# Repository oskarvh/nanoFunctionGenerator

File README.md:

# nanoFunctionGenerator
Arbitrary function generator using the RP2040

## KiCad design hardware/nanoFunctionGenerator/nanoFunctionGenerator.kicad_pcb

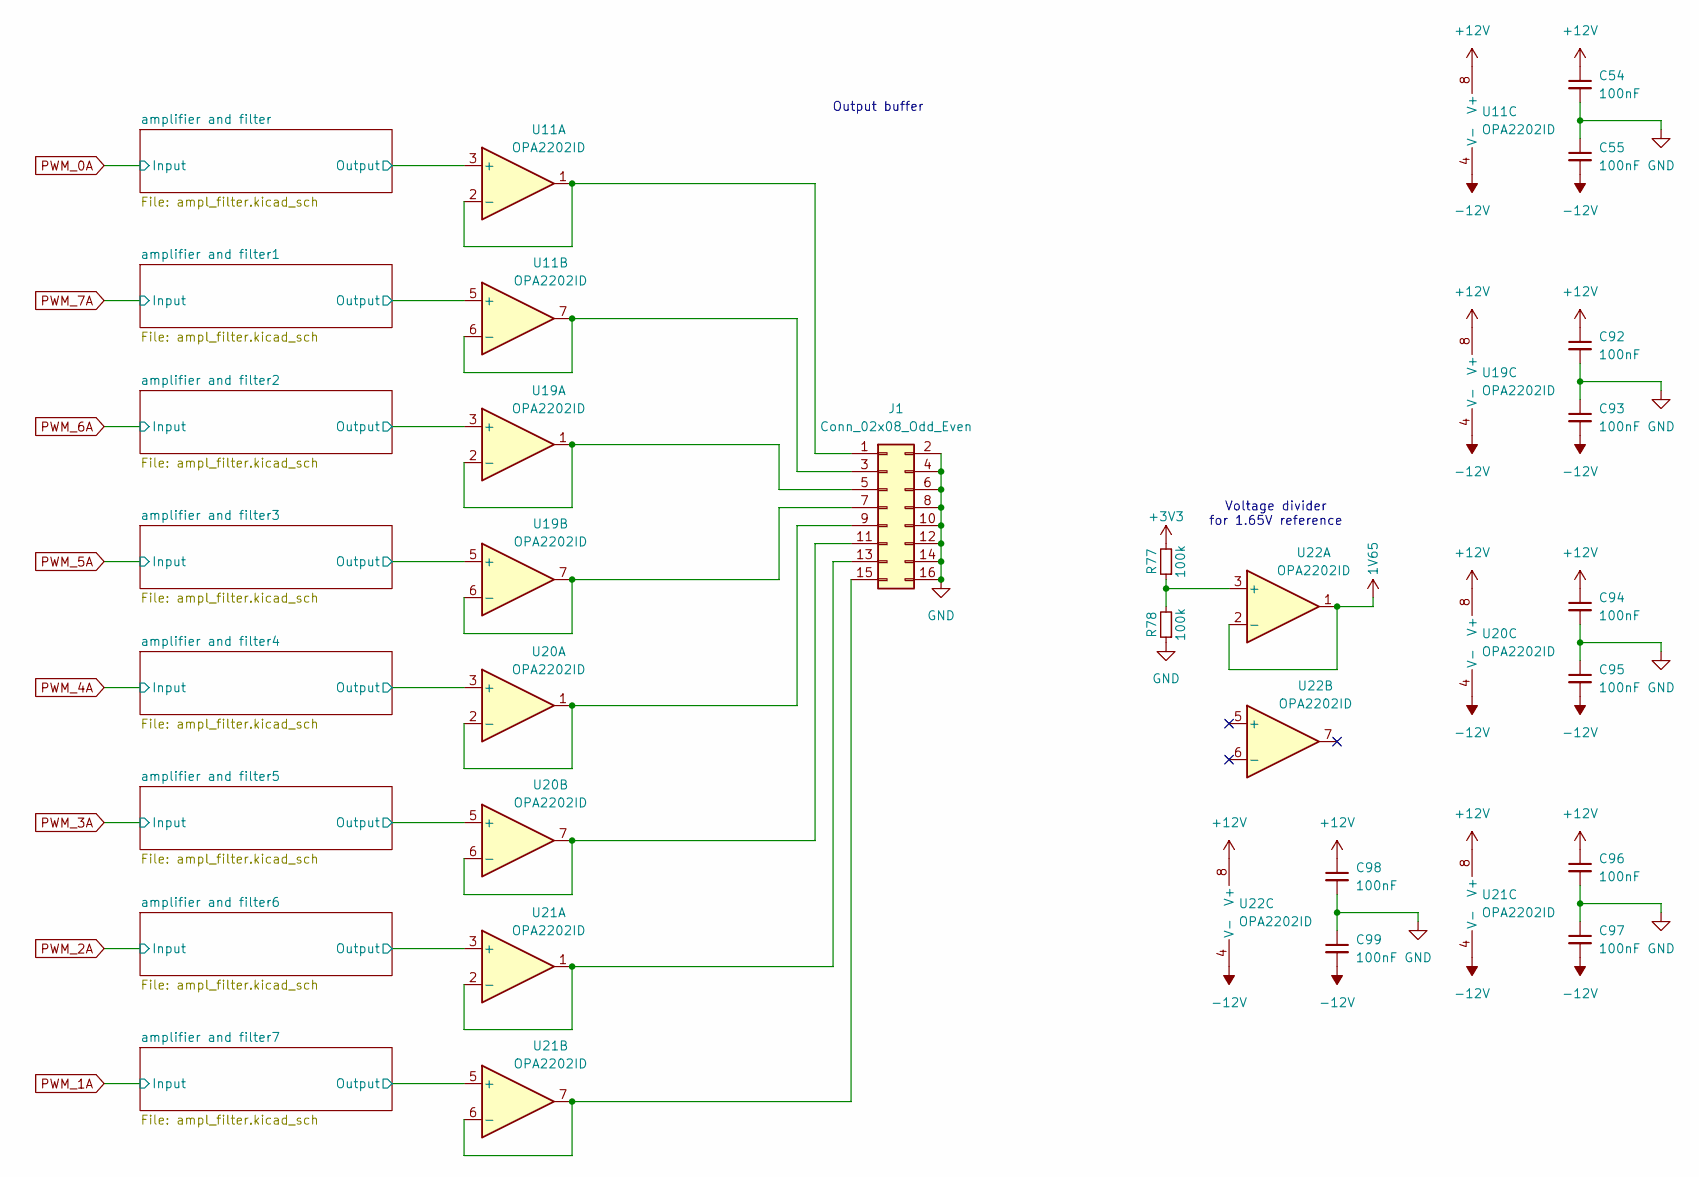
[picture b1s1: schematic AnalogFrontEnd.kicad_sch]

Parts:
C54, C55, C92, C93, C94, C95, C96, C97, C98, C99: 100nF; C_0402_1005Metric
J1: Conn_02x08_Odd_Even; PinHeader_2x08_P2.54mm_Vertical
R77, R78: 100k; R_0402_1005Metric
U11, U19, U20, U21, U22: OPA2202ID; SOIC-8_3.9x4.9mm_P1.27mm

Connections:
1V65: U22.1, U22.2 (-); also elsewhere on the board
+3V3: R77.2; also elsewhere on the board
+12V: C54.1, C92.1, C94.1, C96.1, C98.1, U11.8 (V+), U19.8 (V+), U20.8 (V+), U21.8 (V+), U22.8 (V+); also elsewhere on the board
-12V: C55.2, C93.2, C95.2, C97.2, C99.2, U11.4 (V-), U19.4 (V-), U20.4 (V-), U21.4 (V-), U22.4 (V-); also elsewhere on the board
/AnalogFrontEnd/amplifier and filter1/Output: U11.5 (+); also elsewhere on the board
/AnalogFrontEnd/amplifier and filter2/Output: U19.3 (+); also elsewhere on the board
/AnalogFrontEnd/amplifier and filter3/Output: U19.5 (+); also elsewhere on the board
/AnalogFrontEnd/amplifier and filter4/Output: U20.3 (+); also elsewhere on the board
/AnalogFrontEnd/amplifier and filter5/Output: U20.5 (+); also elsewhere on the board
/AnalogFrontEnd/amplifier and filter6/Output: U21.3 (+); also elsewhere on the board
/AnalogFrontEnd/amplifier and filter7/Output: U21.5 (+); also elsewhere on the board
/AnalogFrontEnd/amplifier and filter/Output: U11.3 (+); also elsewhere on the board
GND: C54.2, C55.1, C92.2, C93.1, C94.2, C95.1, C96.2, C97.1, C98.2, C99.1, J1.2, J1.4, J1.6, J1.8, J1.10, J1.12, J1.14, J1.16, R78.1; also elsewhere on the board
unnamed: J1.1, U11.1, U11.2 (-)
unnamed: J1.3, U11.6 (-), U11.7
unnamed: J1.5, U19.1, U19.2 (-)
unnamed: J1.7, U19.6 (-), U19.7
unnamed: J1.9, U20.1, U20.2 (-)
unnamed: J1.11, U20.6 (-), U20.7
unnamed: J1.13, U21.1, U21.2 (-)
unnamed: J1.15, U21.6 (-), U21.7
unnamed: R77.1, R78.2, U22.3 (+)

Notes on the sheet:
Voltage divider for 1.65V reference
Output buffer

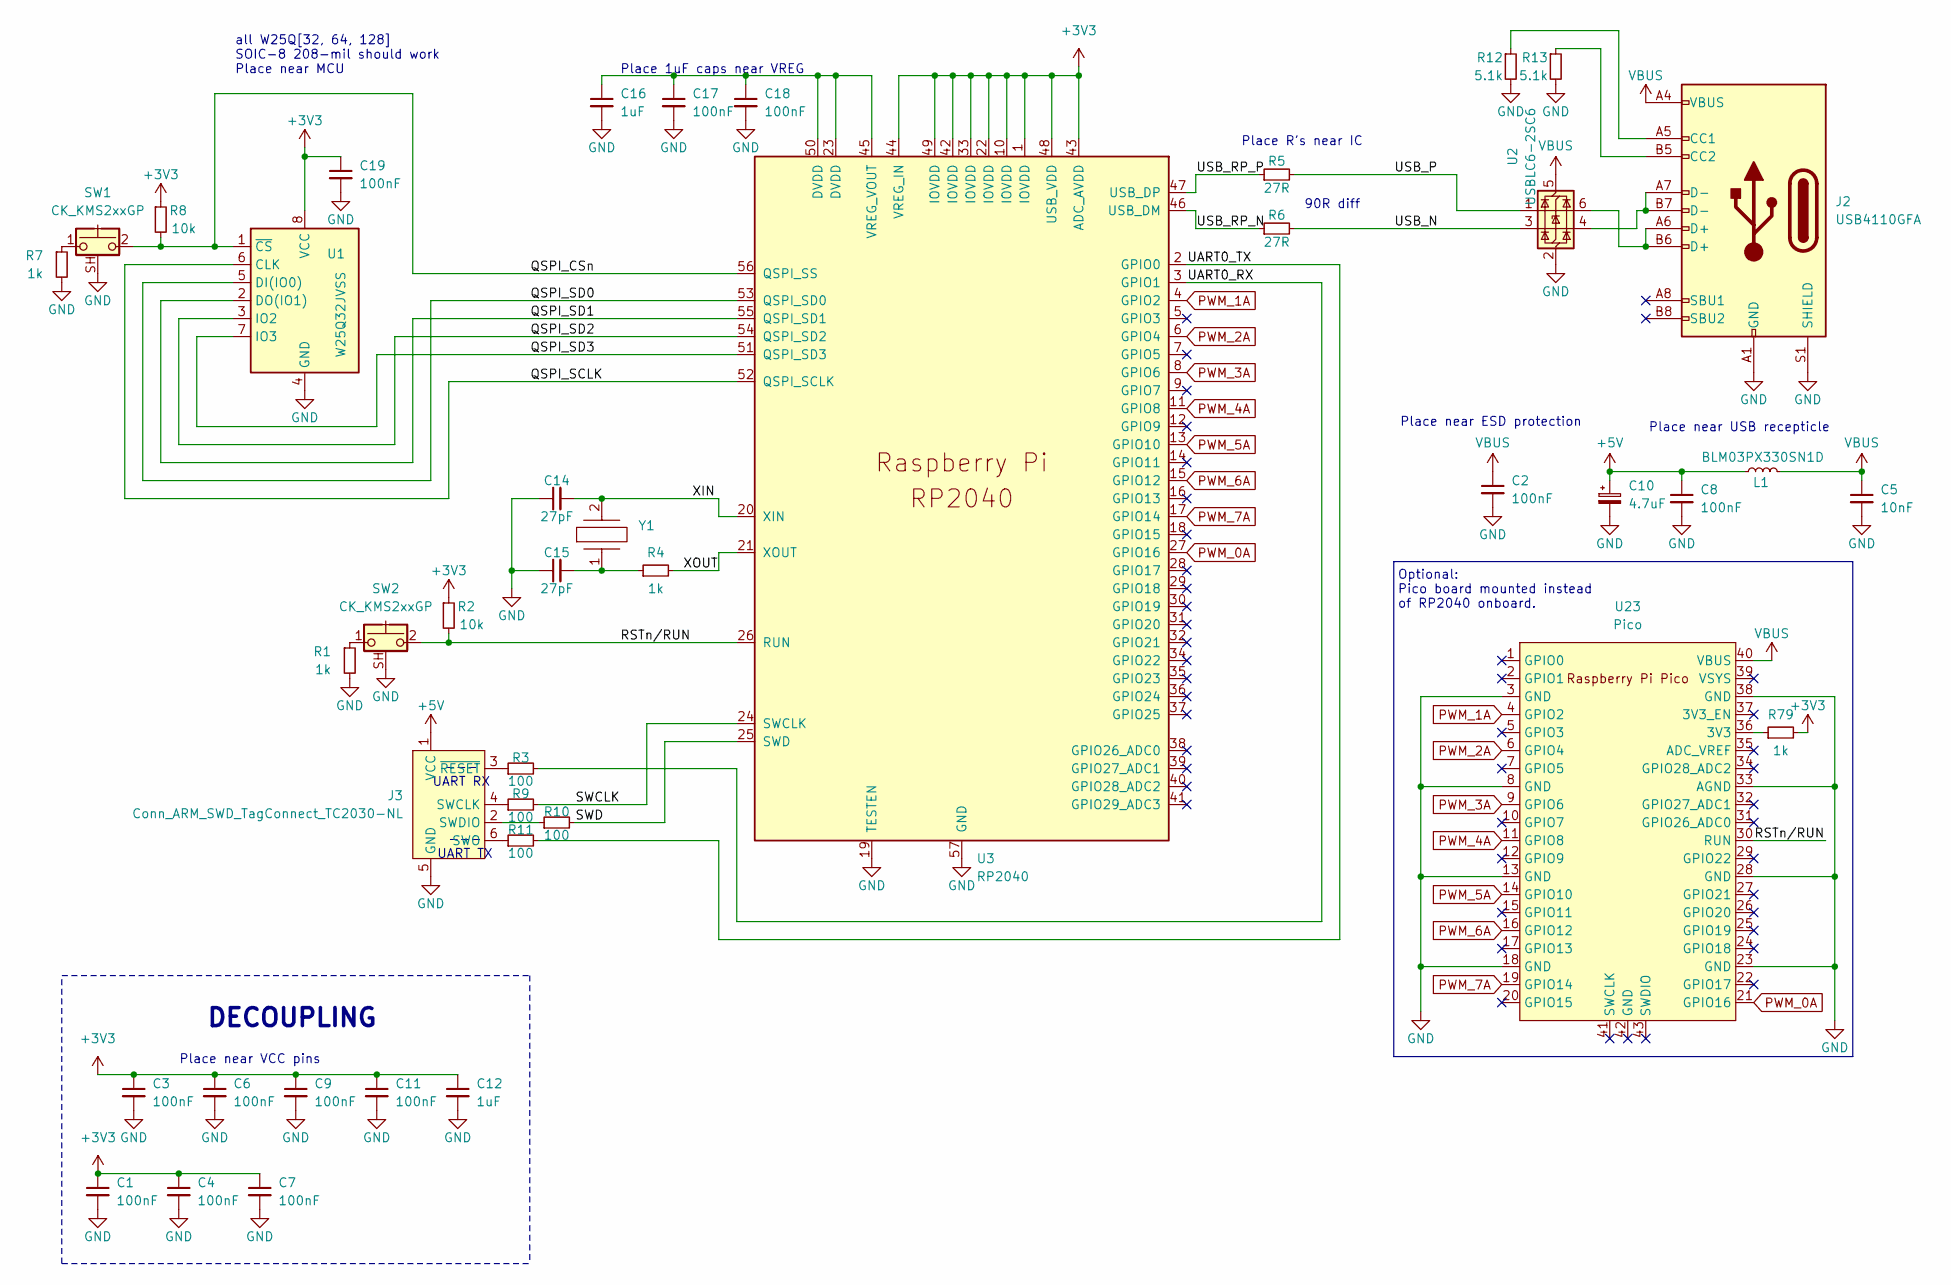
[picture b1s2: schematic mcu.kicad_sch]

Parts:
C1, C2, C3, C4, C6, C7, C8, C9, C11, C17, C18, C19: 100nF; C_0402_1005Metric; LCSC C1525
C5: 10nF; C_0402_1005Metric; LCSC C1525
C10: 4.7uF; C_Elec_4x5.4; Part Number 865080640004
C12, C16: 1uF; C_0402_1005Metric; LCSC C52923
C14, C15: 27pF; C_0402_1005Metric; LCSC C126504
J2: USB4110GFA; USB4110-GF-A_GCT
J3: Conn_ARM_SWD_TagConnect_TC2030-NL; Tag-Connect_TC2030-IDC-NL_2x03_P1.27mm_Vertical
L1: BLM03PX330SN1D; L_0603_1608Metric
R1, R7: 1k; R_0402_1005Metric; LCSC C279981
R2, R8: 10k; R_0402_1005Metric; LCSC C140214
R3, R9, R10, R11: 100; R_0402_1005Metric; LCSC C279981
R4, R79: 1k; R_0402_1005Metric; LCSC C11702
R5, R6: 27R; R_0402_1005Metric; LCSC C25100
R12, R13: 5.1k; R_0402_1005Metric; LCSC C279981
SW1, SW2: CK_KMS2xxGP; SW_SPST_CK_KMS2xxGP
U1: W25Q32JVSS; SOIC-8_5.23x5.23mm_P1.27mm
U2: USBLC6-2SC6; SOT-23-6
U3: RP2040; QFN-56-1EP_7x7mm_P0.4mm_EP3.2x3.2mm_ThermalVias; LCSC C2040
U23: Pico; RPi_Pico_SMD_TH
Y1: 445I23D12M00000; 445I23D12M00000_CTS-L; Mouser Part Number 774-445I23D12M00000

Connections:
+3V3: C1.1, C3.1, C4.1, C6.1, C7.1, C9.1, C11.1, C12.1, C19.1, R2.1, R8.1, R79.2, U1.8 (VCC), U3.1 (IOVDD), U3.10 (IOVDD), U3.22 (IOVDD), U3.33 (IOVDD), U3.42 (IOVDD), U3.43 (ADC_AVDD), U3.44 (VREG_IN), U3.48 (USB_VDD), U3.49 (IOVDD); also elsewhere on the board
+5V: C8.1, C10.1, J3.1 (VCC), L1.1; also elsewhere on the board
/mcu/QSPI_CSn: R8.2, SW1.2, U1.1 (~CS), U3.56 (QSPI_SS)
/mcu/QSPI_SCLK: U1.6 (CLK), U3.52 (QSPI_SCLK)
/mcu/QSPI_SD0: U1.5 (DI(IO0)), U3.53 (QSPI_SD0)
/mcu/QSPI_SD1: U1.2 (DO(IO1)), U3.55 (QSPI_SD1)
/mcu/QSPI_SD2: U1.3 (IO2), U3.54 (QSPI_SD2)
/mcu/QSPI_SD3: U1.7 (IO3), U3.51 (QSPI_SD3)
/mcu/RSTn/RUN: R2.2, SW2.2, U3.26 (RUN), U23.30 (RUN)
/mcu/SWCLK: R9.2, U3.24 (SWCLK)
/mcu/SWD: R10.2, U3.25 (SWD)
/mcu/UART0_RX: R3.2, U3.3 (GPIO1)
/mcu/UART0_TX: R11.2, U3.2 (GPIO0)
/mcu/USB_N: R6.2, U2.3 (I/O2)
/mcu/USB_P: R5.2, U2.1 (I/O1)
/mcu/USB_RP_N: R6.1, U3.46 (USB_DM)
/mcu/USB_RP_P: R5.1, U3.47 (USB_DP)
/mcu/XIN: C14.2, U3.20 (XIN), Y1.2
/mcu/XOUT: R4.2, U3.21 (XOUT)
GND: C1.2, C2.2, C3.2, C4.2, C5.2, C6.2, C7.2, C8.2, C9.2, C10.2, C11.2, C12.2, C14.1, C15.1, C16.2, C17.2, C18.2, C19.2, J2.A1 (GND), J2.A12 (GND), J2.B1 (GND), J2.B12 (GND), J2.S1 (SHIELD), J3.5 (GND), R1.2, R7.2, R12.2, R13.2, SW1.SH (B), SW2.SH (B), U1.4 (GND), U2.2 (GND), U3.19 (TESTEN), U3.57 (GND), U23.3 (GND), U23.8 (GND), U23.13 (GND), U23.18 (GND), U23.23 (GND), U23.28 (GND), U23.33 (AGND), U23.38 (GND); also elsewhere on the board
unnamed: C15.2, R4.1, Y1.1
unnamed: J2.A5 (CC1), R12.1
unnamed: J2.B5 (CC2), R13.1
unnamed: J2.A6 (D+), J2.B6 (D+), U2.6 (I/O1)
unnamed: J2.A7 (D-), J2.B7 (D-), U2.4 (I/O2)
unnamed: J3.4 (SWCLK), R9.1
unnamed: J3.2 (SWDIO), R10.1
unnamed: J3.6 (SWO), R11.1
unnamed: J3.3 (~RESET), R3.1
unnamed: R1.1, SW2.1
unnamed: R7.1, SW1.1
unnamed: C16.1, C17.1, C18.1, U3.23 (DVDD), U3.45 (VREG_VOUT), U3.50 (DVDD)
unnamed: R79.1, U23.36 (3V3)
PWM_0A: U3.27 (GPIO16), U23.21 (GPIO16); also elsewhere on the board
PWM_1A: U3.4 (GPIO2), U23.4 (GPIO2); also elsewhere on the board
PWM_2A: U3.6 (GPIO4), U23.6 (GPIO4); also elsewhere on the board
PWM_3A: U3.8 (GPIO6), U23.9 (GPIO6); also elsewhere on the board
PWM_4A: U3.11 (GPIO8), U23.11 (GPIO8); also elsewhere on the board
PWM_5A: U3.13 (GPIO10), U23.14 (GPIO10); also elsewhere on the board
PWM_6A: U3.15 (GPIO12), U23.16 (GPIO12); also elsewhere on the board
PWM_7A: U3.17 (GPIO14), U23.19 (GPIO14); also elsewhere on the board
VBUS: C2.1, C5.1, J2.A4 (VBUS), J2.A9 (VBUS), J2.B4 (VBUS), J2.B9 (VBUS), L1.2, U2.5 (VBUS), U23.40 (VBUS)

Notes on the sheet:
Place near USB recepticle
Place R's near IC
--- UART TX
Optional: Pico board mounted instead of RP2040 onboard.
--- UART RX
Place near ESD protection
all W25Q[32, 64, 128] SOIC-8 208-mil should work Place near MCU
Place 1uF caps near VREG
Place near VCC pins
90R diff
DECOUPLING

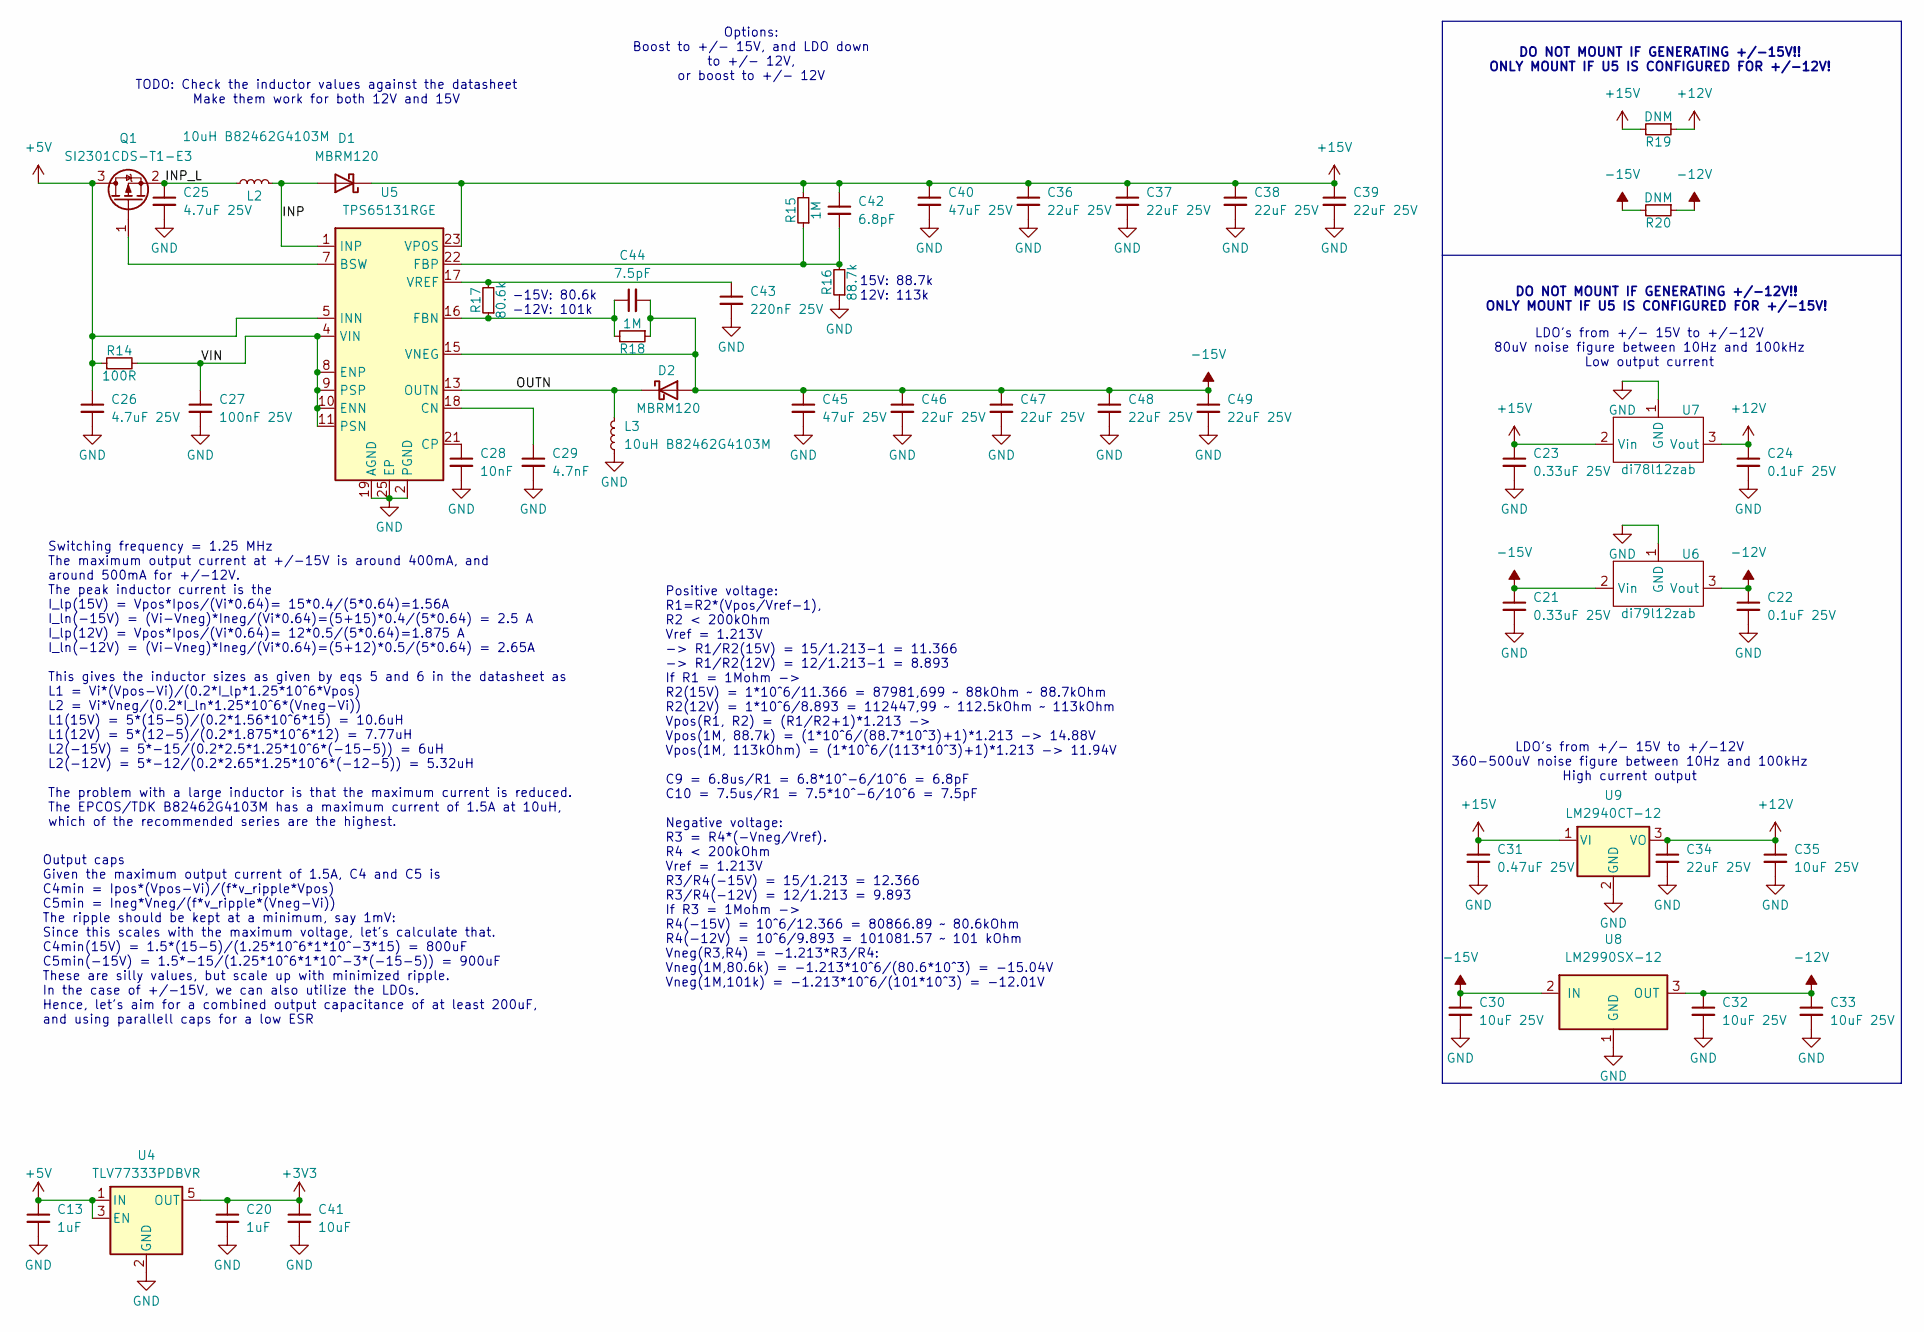
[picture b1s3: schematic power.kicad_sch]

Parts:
C13, C20: 1uF; C_0603_1608Metric
C21, C23: 0.33uF 25V; C_0603_1608Metric
C22, C24: 0.1uF 25V; C_0603_1608Metric
C25, C26: 4.7uF 25V; C_0805_2012Metric
C27: 100nF 25V; C_0402_1005Metric
C28: 10nF; C_0402_1005Metric
C29: 4.7nF; C_0402_1005Metric
C30, C32, C33, C35: 10uF 25V; C_0805_2012Metric
C31: 0.47uF 25V; C_0603_1608Metric
C34, C36, C37, C38, C39, C46, C47, C48, C49: 22uF 25V; C_0805_2012Metric
C40, C45: 47uF 25V; C_1206_3216Metric
C41: 10uF; C_0603_1608Metric
C42: 6.8pF; C_0402_1005Metric
C43: 220nF 25V; C_0402_1005Metric
C44: 7.5pF; C_0402_1005Metric
D1, D2: MBRM120
L2, L3: 10uH B82462G4103M; L_Vishay_IHLP-2525
Q1: SI2301CDS-T1-E3; SOT-23
R14: 100R; R_0402_1005Metric
R15, R18: 1M; R_0402_1005Metric
R16: 88.7k; R_0402_1005Metric
R17: 80.6k; R_0402_1005Metric
R19, R20: DNM; R_0402_1005Metric
U4: TLV77333PDBVR; SOT-23-5
U5: TPS65131RGE; VQFN-24-1EP_4x4mm_P0.5mm_EP2.45x2.45mm_ThermalVias
U6: di79l12zab; TO-92
U7: di78l12zab; TO-92
U8: LM2990SX-12; TO-220-3_no_hole
U9: LM2940CT-12; TO-220-3_no_hole

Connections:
+3V3: C20.1, C41.1, U4.5 (OUT); also elsewhere on the board
+5V: C13.1, C26.1, Q1.3 (D), R14.1, U4.1 (IN), U4.3 (EN), U5.5 (INN), U5.6 (INN); also elsewhere on the board
+12V: C24.1, C34.1, C35.1, R19.1, U7.3 (Vout), U9.3 (VO); also elsewhere on the board
+15V: C23.1, C31.1, C36.1, C37.1, C38.1, C39.1, C40.1, C42.1, D1.1 (K), R15.2, R19.2, U5.23 (VPOS), U7.2 (Vin), U9.1 (VI)
-12V: C22.1, C32.1, C33.1, R20.1, U6.3 (Vout), U8.3 (OUT); also elsewhere on the board
-15V: C21.1, C30.1, C44.2, C45.1, C46.1, C47.1, C48.1, C49.1, D2.2 (A), R18.1, R20.2, U5.15 (VNEG), U6.2 (Vin), U8.2 (IN)
/power/INP: D1.2 (A), L2.2, U5.1 (INP), U5.24 (INP)
/power/INP_L: C25.1, L2.1, Q1.2 (S)
/power/OUTN: D2.1 (K), L3.2, U5.13 (OUTN), U5.14 (OUTN)
/power/VIN: C27.1, R14.2, U5.4 (VIN), U5.8 (ENP), U5.9 (PSP), U5.10 (ENN), U5.11 (PSN)
GND: C13.2, C20.2, C21.2, C22.2, C23.2, C24.2, C25.2, C26.2, C27.2, C28.2, C29.2, C30.2, C31.2, C32.2, C33.2, C34.2, C35.2, C36.2, C37.2, C38.2, C39.2, C40.2, C41.2, C43.2, C45.2, C46.2, C47.2, C48.2, C49.2, L3.1, R16.1, U4.2 (GND), U5.2 (PGND), U5.3 (PGND), U5.19 (AGND), U5.25 (EP), U6.1 (GND), U7.1 (GND), U8.1 (GND), U9.2 (GND); also elsewhere on the board
unnamed: Q1.1 (G), U5.7 (BSW)
unnamed: C29.1, U5.18 (CN)
unnamed: C28.1, U5.21 (CP)
unnamed: C44.1, R17.1, R18.2, U5.16 (FBN)
unnamed: C42.2, R15.1, R16.2, U5.22 (FBP)
unnamed: C43.1, R17.2, U5.17 (VREF)

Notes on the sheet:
Switching frequency = 1.25 MHz The maximum output current at +/-15V is around 400mA, and around 500mA for +/-12V. The peak inductor current is the I_lp(15V) = Vpos*Ipos/(Vi*0.64)= 15*0.4/(5*0.64)=1.56A I_ln(-15V) = (Vi-Vneg)*Ineg/(Vi*0.64)=(5+15)*0.4/(5*0.64) = 2.5 A I_lp(12V) = Vpos*Ipos/(Vi*0.64)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
DO NOT MOUNT IF GENERATING +/-15V!! ONLY MOUNT IF U5 IS CONFIGURED FOR +/-12V!
LDO's from +/- 15V to +/-12V 80uV noise figure between 10Hz and 100kHz Low output current
Output caps Given the maximum output current of 1.5A, C4 and C5 is C4min = Ipos*(Vpos-Vi)/(f*v_ripple*Vpos) C5min = Ineg*Vneg/(f*v_ripple*(Vneg-Vi)) The ripple should be kept at a minimum, say 1mV: Since this scales with the maximum voltage, let's calculate that. C4min(15V) = 1.5*(15-5)/(1.25*10^6*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
-15V: 80.6k -12V: 101k
Positive voltage: R1=R2*(Vpos/Vref-1), R2 < 200kOhm Vref = 1.213V -> R1/R2(15V) = 15/1.213-1 = 11.366 -> R1/R2(12V) = 12/1.213-1 = 8.893 If R1 = 1Mohm -> R2(15V) = 1*10^6/11.366 = 87981,699 ~ 88kOhm ~ 88.7kOhm R2(12V) = 1*10^6/8.893 = 112447,99 ~ 112.5kOhm ~ 113kOhm Vpos(R1, R2) = (R1/R2+1)*1.213 -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
LDO's from +/- 15V to +/-12V 360-500uV noise figure between 10Hz and 100kHz High current output
DO NOT MOUNT IF GENERATING +/-12V!! ONLY MOUNT IF U5 IS CONFIGURED FOR +/-15V!
TODO: Check the inductor values against the datasheet Make them work for both 12V and 15V
Options: Boost to +/- 15V, and LDO down to +/- 12V, or boost to +/- 12V
15V: 88.7k 12V: 113k

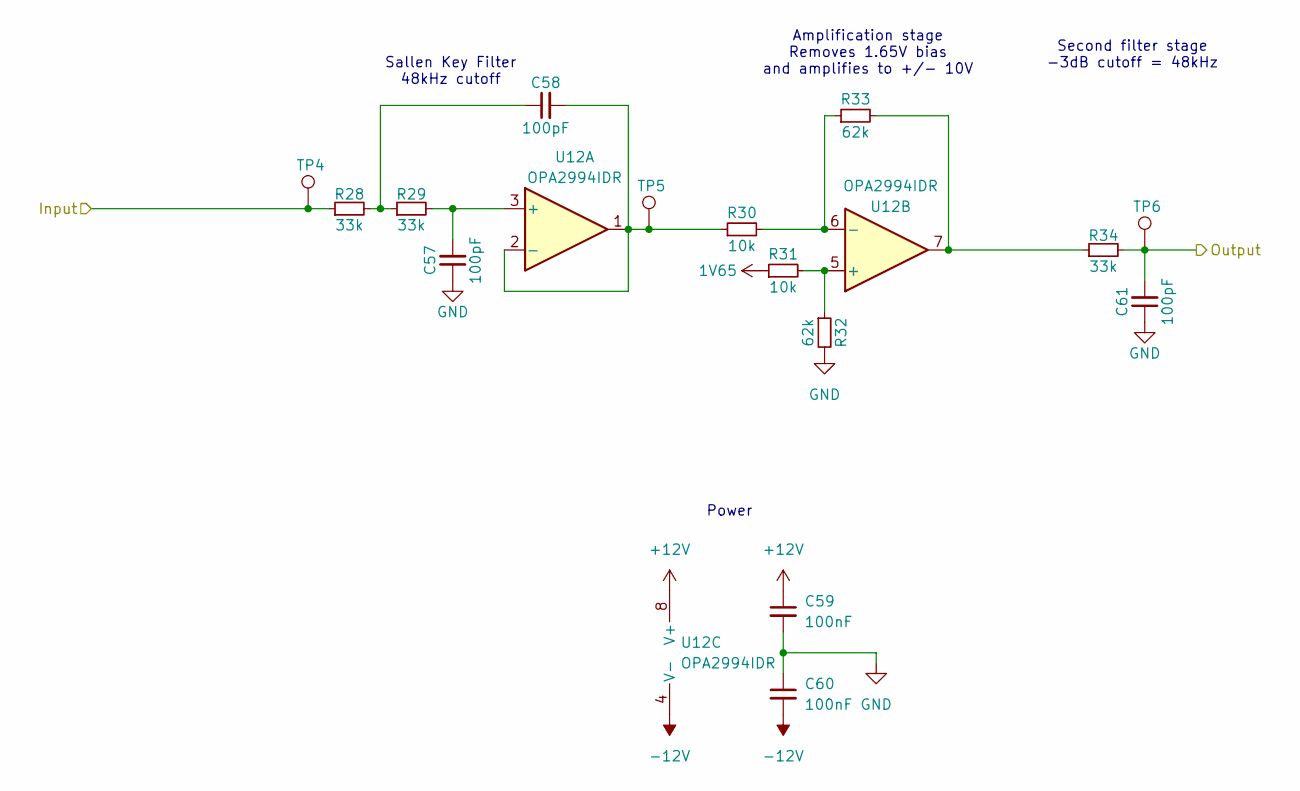
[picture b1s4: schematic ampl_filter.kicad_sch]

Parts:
C57, C58, C61: 100pF; C_0402_1005Metric
C59, C60: 100nF; C_0402_1005Metric
R28, R29, R34: 33k; R_0402_1005Metric
R30, R31: 10k; R_0402_1005Metric
R32, R33: 62k; R_0402_1005Metric
TP4, TP5, TP6: TestPoint; TestPoint_Pad_D1.5mm
U12: OPA2994IDR; SOIC-8_3.9x4.9mm_P1.27mm

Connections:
1V65: R31.1; also elsewhere on the board
+12V: C59.1, U12.8 (V+); also elsewhere on the board
-12V: C60.2, U12.4 (V-); also elsewhere on the board
/AnalogFrontEnd/amplifier and filter1/Output: C61.2, R34.2, TP6.1; also elsewhere on the board
GND: C57.1, C59.2, C60.1, C61.1, R32.2; also elsewhere on the board
unnamed: C58.1, R28.2, R29.1
unnamed: R33.2, R34.1, U12.7
unnamed: C57.2, R29.2, U12.3 (+)
unnamed: C58.2, R30.1, TP5.1, U12.1, U12.2 (-)
unnamed: R31.2, R32.1, U12.5 (+)
unnamed: R30.2, R33.1, U12.6 (-)
PWM_7A: R28.1, TP4.1; also elsewhere on the board

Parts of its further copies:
C50, C51, C56, C62, C63, C66, C67, C68, C71, C72, C73, C76, C77, C78, C81, C82, C83, C86, C87, C88, C91: 100pF; C_0402_1005Metric
C52, C53, C64, C65, C69, C70, C74, C75, C79, C80, C84, C85, C89, C90: 100nF; C_0402_1005Metric
R21, R22, R27, R35, R36, R41, R42, R43, R48, R49, R50, R55, R56, R57, R62, R63, R64, R69, R70, R71, R76: 33k; R_0402_1005Metric
R23, R24, R37, R38, R44, R45, R51, R52, R58, R59, R65, R66, R72, R73: 10k; R_0402_1005Metric
R25, R26, R39, R40, R46, R47, R53, R54, R60, R61, R67, R68, R74, R75: 62k; R_0402_1005Metric
TP1, TP2, TP3, TP7, TP8, TP9, TP10, TP11, TP12, TP13, TP14, TP15, TP16, TP17, TP18, TP19, TP20, TP21, TP22, TP23, TP24: TestPoint; TestPoint_Pad_D1.5mm
U10, U13, U14, U15, U16, U17, U18: OPA2994IDR; SOIC-8_3.9x4.9mm_P1.27mm

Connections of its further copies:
1V65: R24.1, R38.1, R45.1, R52.1, R59.1, R66.1, R73.1; also elsewhere on the board
+12V: C52.1, C64.1, C69.1, C74.1, C79.1, C84.1, C89.1, U10.8 (V+), U13.8 (V+), U14.8 (V+), U15.8 (V+), U16.8 (V+), U17.8 (V+), U18.8 (V+); also elsewhere on the board
-12V: C53.2, C65.2, C70.2, C75.2, C80.2, C85.2, C90.2, U10.4 (V-), U13.4 (V-), U14.4 (V-), U15.4 (V-), U16.4 (V-), U17.4 (V-), U18.4 (V-); also elsewhere on the board
/AnalogFrontEnd/amplifier and filter2/Output: C66.2, R41.2, TP9.1; also elsewhere on the board
/AnalogFrontEnd/amplifier and filter3/Output: C71.2, R48.2, TP12.1; also elsewhere on the board
/AnalogFrontEnd/amplifier and filter4/Output: C76.2, R55.2, TP15.1; also elsewhere on the board
/AnalogFrontEnd/amplifier and filter5/Output: C81.2, R62.2, TP18.1; also elsewhere on the board
/AnalogFrontEnd/amplifier and filter6/Output: C86.2, R69.2, TP21.1; also elsewhere on the board
/AnalogFrontEnd/amplifier and filter7/Output: C91.2, R76.2, TP24.1; also elsewhere on the board
/AnalogFrontEnd/amplifier and filter/Output: C56.2, R27.2, TP3.1; also elsewhere on the board
GND: C50.1, C52.2, C53.1, C56.1, C62.1, C64.2, C65.1, C66.1, C67.1, C69.2, C70.1, C71.1, C72.1, C74.2, C75.1, C76.1, C77.1, C79.2, C80.1, C81.1, C82.1, C84.2, C85.1, C86.1, C87.1, C89.2, C90.1, C91.1, R25.2, R39.2, R46.2, R53.2, R60.2, R67.2, R74.2; also elsewhere on the board
unnamed: C51.1, R21.2, R22.1
unnamed: C63.1, R35.2, R36.1
unnamed: C68.1, R42.2, R43.1
unnamed: C73.1, R49.2, R50.1
unnamed: C78.1, R56.2, R57.1
unnamed: C83.1, R63.2, R64.1
unnamed: C88.1, R70.2, R71.1
unnamed: R26.2, R27.1, U10.7
unnamed: R40.2, R41.1, U13.7
unnamed: R47.2, R48.1, U14.7
unnamed: R54.2, R55.1, U15.7
unnamed: R61.2, R62.1, U16.7
unnamed: R68.2, R69.1, U17.7
unnamed: R75.2, R76.1, U18.7
unnamed: C50.2, R22.2, U10.3 (+)
unnamed: C51.2, R23.1, TP2.1, U10.1, U10.2 (-)
unnamed: R24.2, R25.1, U10.5 (+)
unnamed: R23.2, R26.1, U10.6 (-)
unnamed: C62.2, R36.2, U13.3 (+)
unnamed: C63.2, R37.1, TP8.1, U13.1, U13.2 (-)
unnamed: R38.2, R39.1, U13.5 (+)
unnamed: R37.2, R40.1, U13.6 (-)
unnamed: C67.2, R43.2, U14.3 (+)
unnamed: C68.2, R44.1, TP11.1, U14.1, U14.2 (-)
unnamed: R45.2, R46.1, U14.5 (+)
unnamed: R44.2, R47.1, U14.6 (-)
unnamed: C72.2, R50.2, U15.3 (+)
unnamed: C73.2, R51.1, TP14.1, U15.1, U15.2 (-)
unnamed: R52.2, R53.1, U15.5 (+)
unnamed: R51.2, R54.1, U15.6 (-)
unnamed: C77.2, R57.2, U16.3 (+)
unnamed: C78.2, R58.1, TP17.1, U16.1, U16.2 (-)
unnamed: R59.2, R60.1, U16.5 (+)
unnamed: R58.2, R61.1, U16.6 (-)
unnamed: C82.2, R64.2, U17.3 (+)
unnamed: C83.2, R65.1, TP20.1, U17.1, U17.2 (-)
unnamed: R66.2, R67.1, U17.5 (+)
unnamed: R65.2, R68.1, U17.6 (-)
unnamed: C87.2, R71.2, U18.3 (+)
unnamed: C88.2, R72.1, TP23.1, U18.1, U18.2 (-)
unnamed: R73.2, R74.1, U18.5 (+)
unnamed: R72.2, R75.1, U18.6 (-)
PWM_0A: R21.1, TP1.1; also elsewhere on the board
PWM_1A: R70.1, TP22.1; also elsewhere on the board
PWM_2A: R63.1, TP19.1; also elsewhere on the board
PWM_3A: R56.1, TP16.1; also elsewhere on the board
PWM_4A: R49.1, TP13.1; also elsewhere on the board
PWM_5A: R42.1, TP10.1; also elsewhere on the board
PWM_6A: R35.1, TP7.1; also elsewhere on the board

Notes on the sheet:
Amplification stage Removes 1.65V bias and amplifies to +/- 10V
Second filter stage -3dB cutoff = 48kHz
Sallen Key Filter 48kHz cutoff
Power

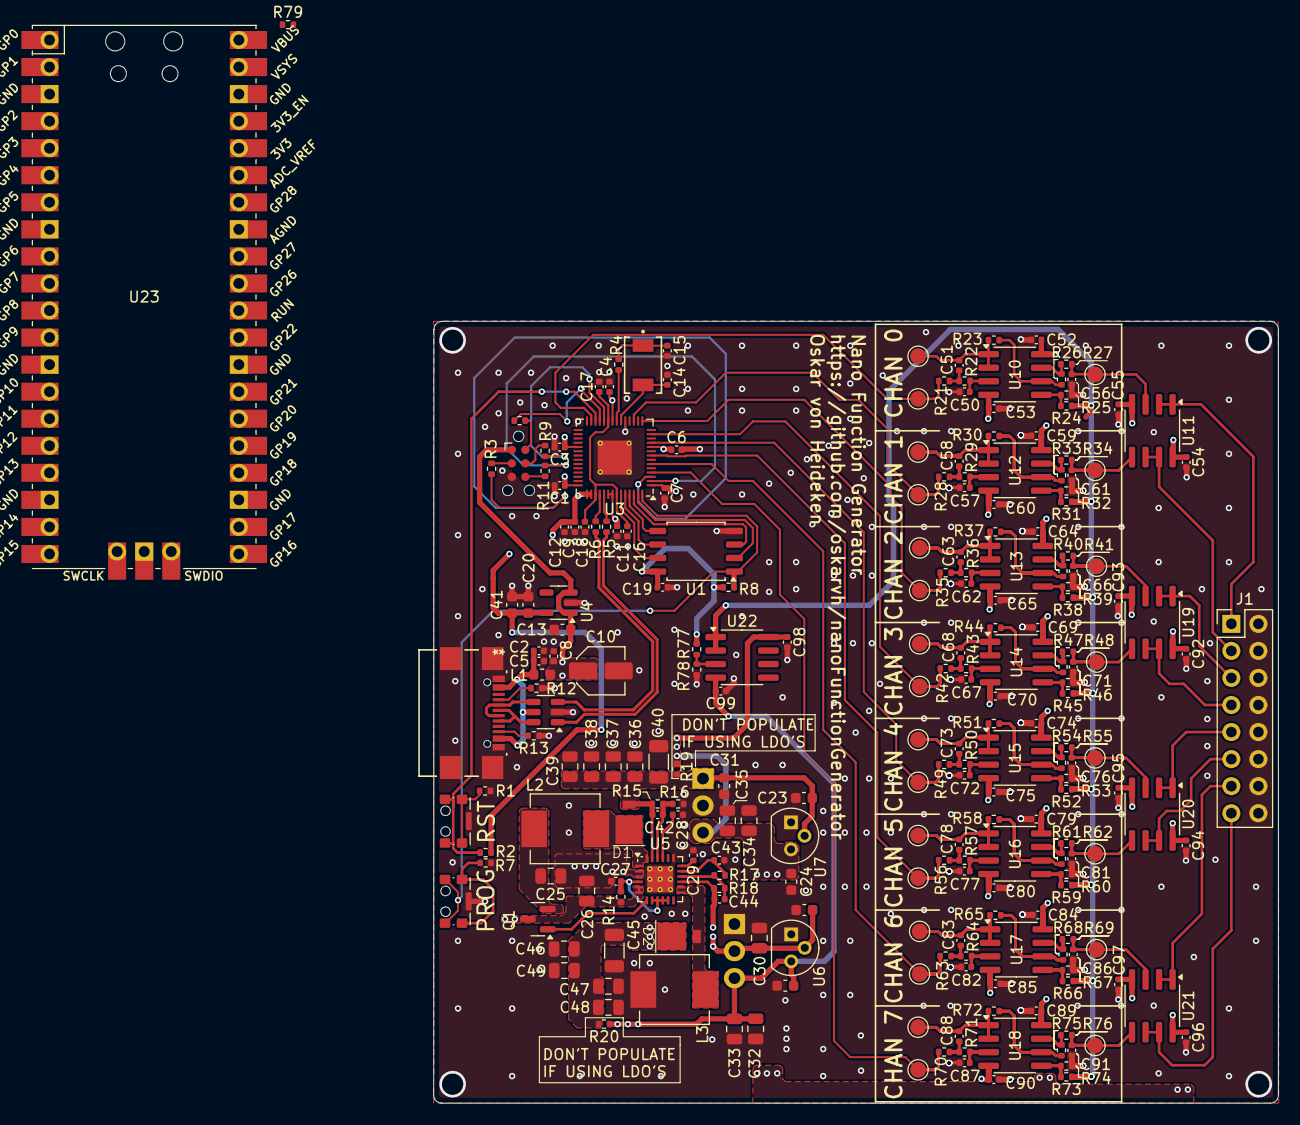
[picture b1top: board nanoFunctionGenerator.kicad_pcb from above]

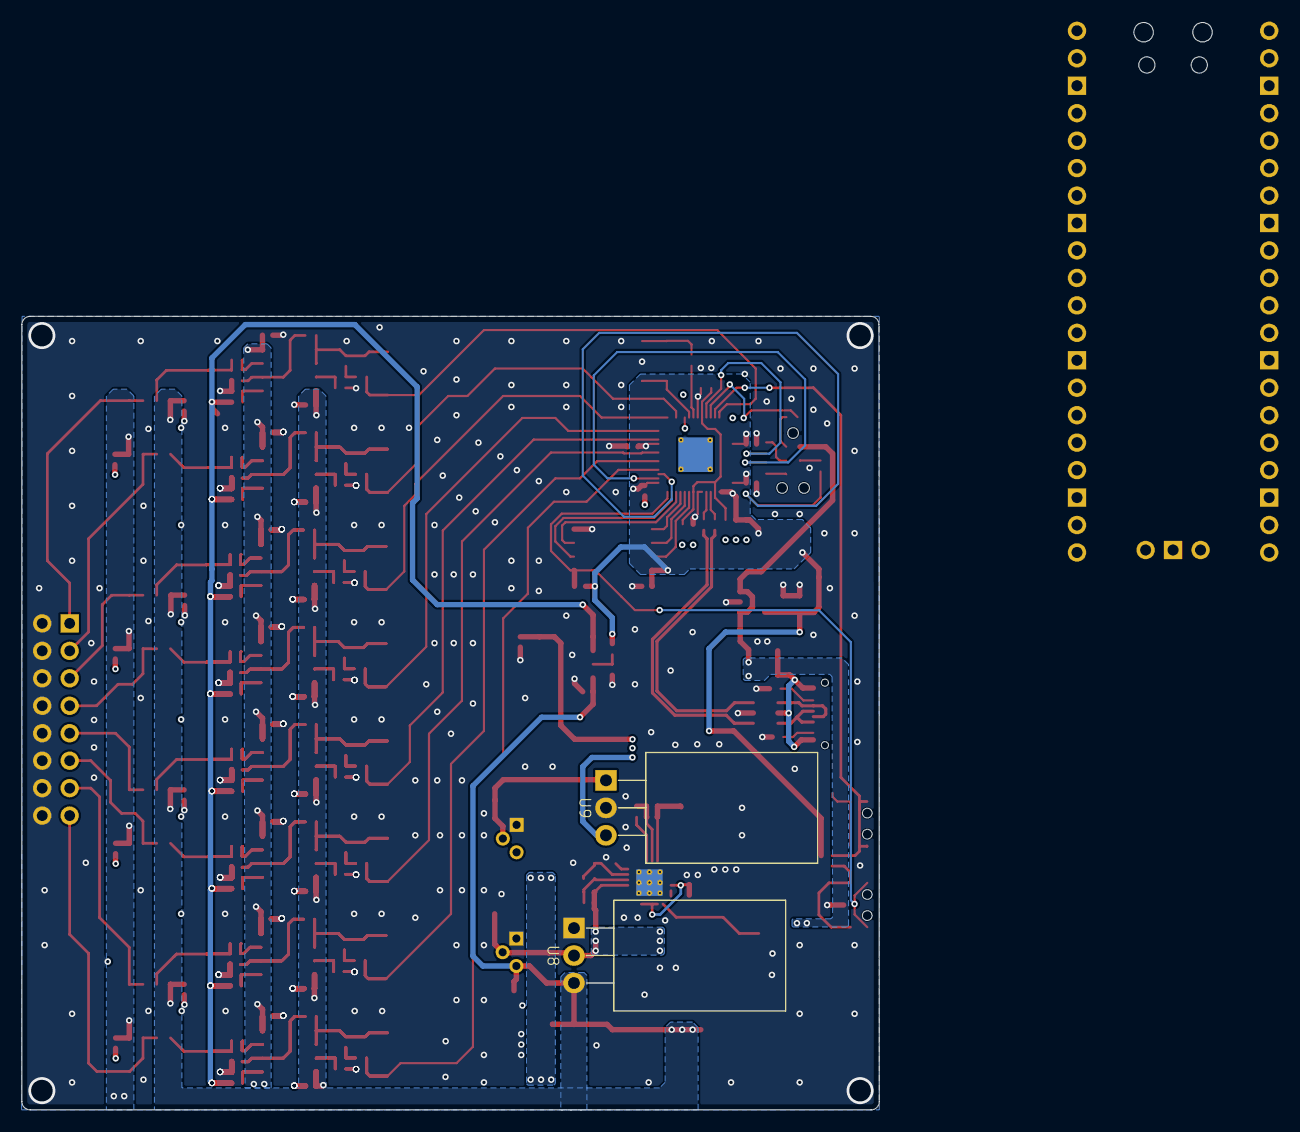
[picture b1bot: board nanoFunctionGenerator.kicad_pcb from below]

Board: 4 copper layers, 79.3 x 73.4 mm, 237 parts (2 on the bottom side), 122 nets.

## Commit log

2025-03-09 Added freeRTOS config for RP2040
2025-03-09 Added vscode debug config
2025-03-10 Added function to read strings, plus started adding the scpi commands
2025-03-10 Initial results with scpi works. *IDN tested and write function was called
2025-03-10 Custom scpi command works as well. Removed some of the unused functions
2025-03-11 Started adding PWM outputs. They are now up and running.
2025-03-12 Added script to calculate the PWM signal
2025-03-12 Did some cleanup of the scripts
2025-03-14 Added some more math
2025-03-15 Added filtering to the PWM signal to resolve the sine wave
2025-03-16 PWM sine wave with DMA now works
2025-03-16 Able to produce full sine wave.
2025-03-16 square, triangle and saw wave implemented.
2025-03-17 Reconfiguring the device over SCPI now works. Only DC level implemented so far, but the rest will follow shortly
2025-03-17 All functions implemented, however switching function currently runs into issues.
2025-03-19 Reconfig of channels now work thanks to a forum post on how to abort the DMA channels
2025-07-07 changing computers
